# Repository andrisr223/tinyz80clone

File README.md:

# tinyz80clone

A Z80 board based on [tiny z80](https://github.com/skiselev/tiny_z80) and [
2063-Z80](https://github.com/Z80-Retro/2063-Z80).
For glue logic SLG46826V is used (a single cpld with more legs/gates would be more appropriate).

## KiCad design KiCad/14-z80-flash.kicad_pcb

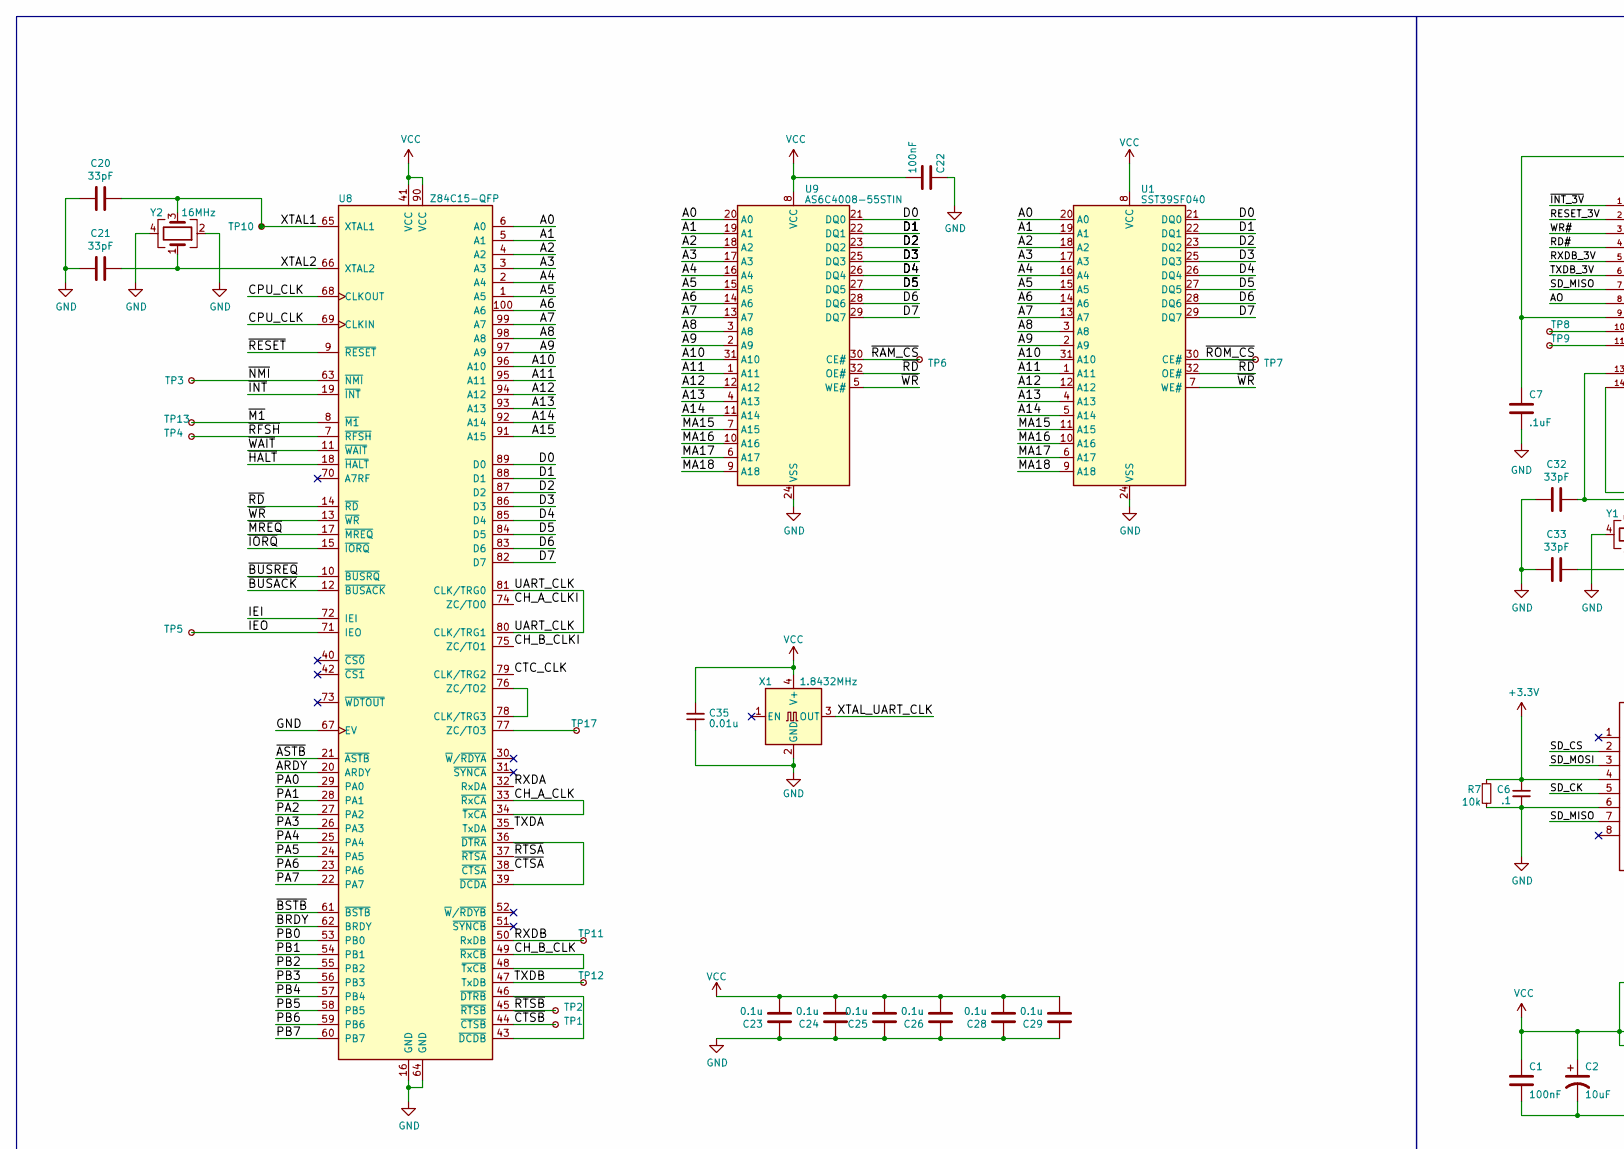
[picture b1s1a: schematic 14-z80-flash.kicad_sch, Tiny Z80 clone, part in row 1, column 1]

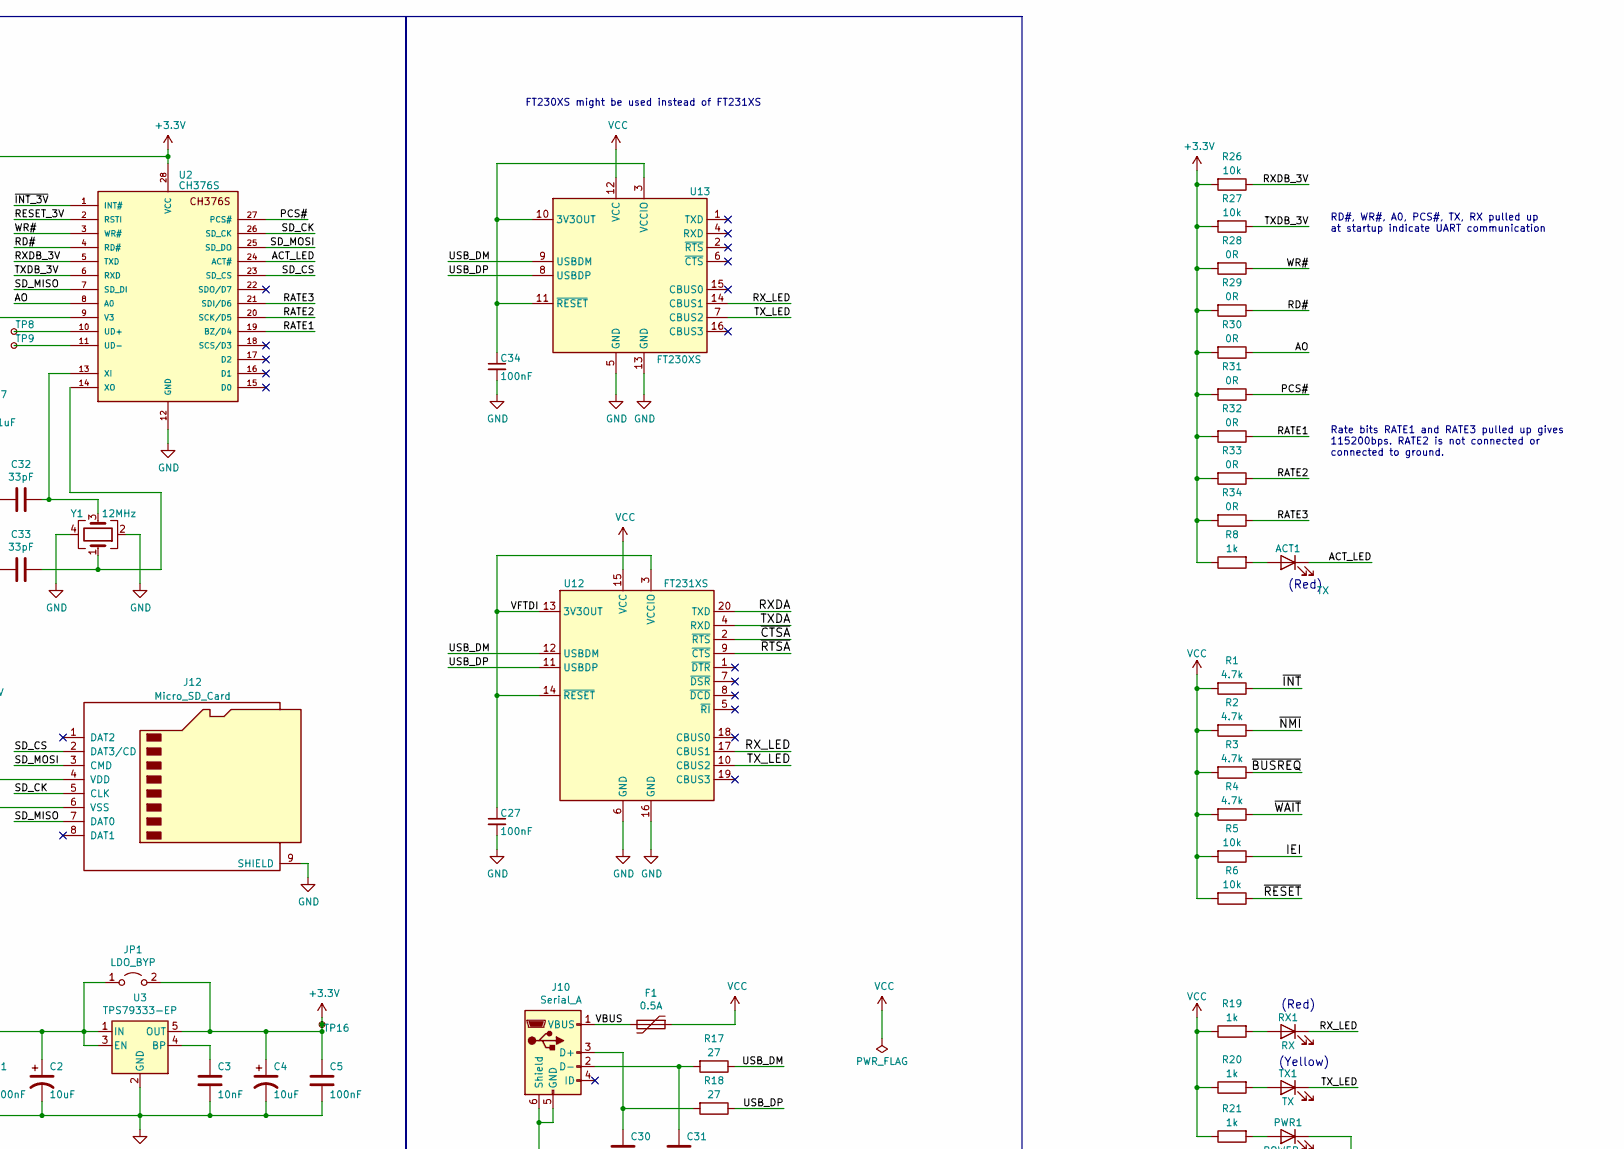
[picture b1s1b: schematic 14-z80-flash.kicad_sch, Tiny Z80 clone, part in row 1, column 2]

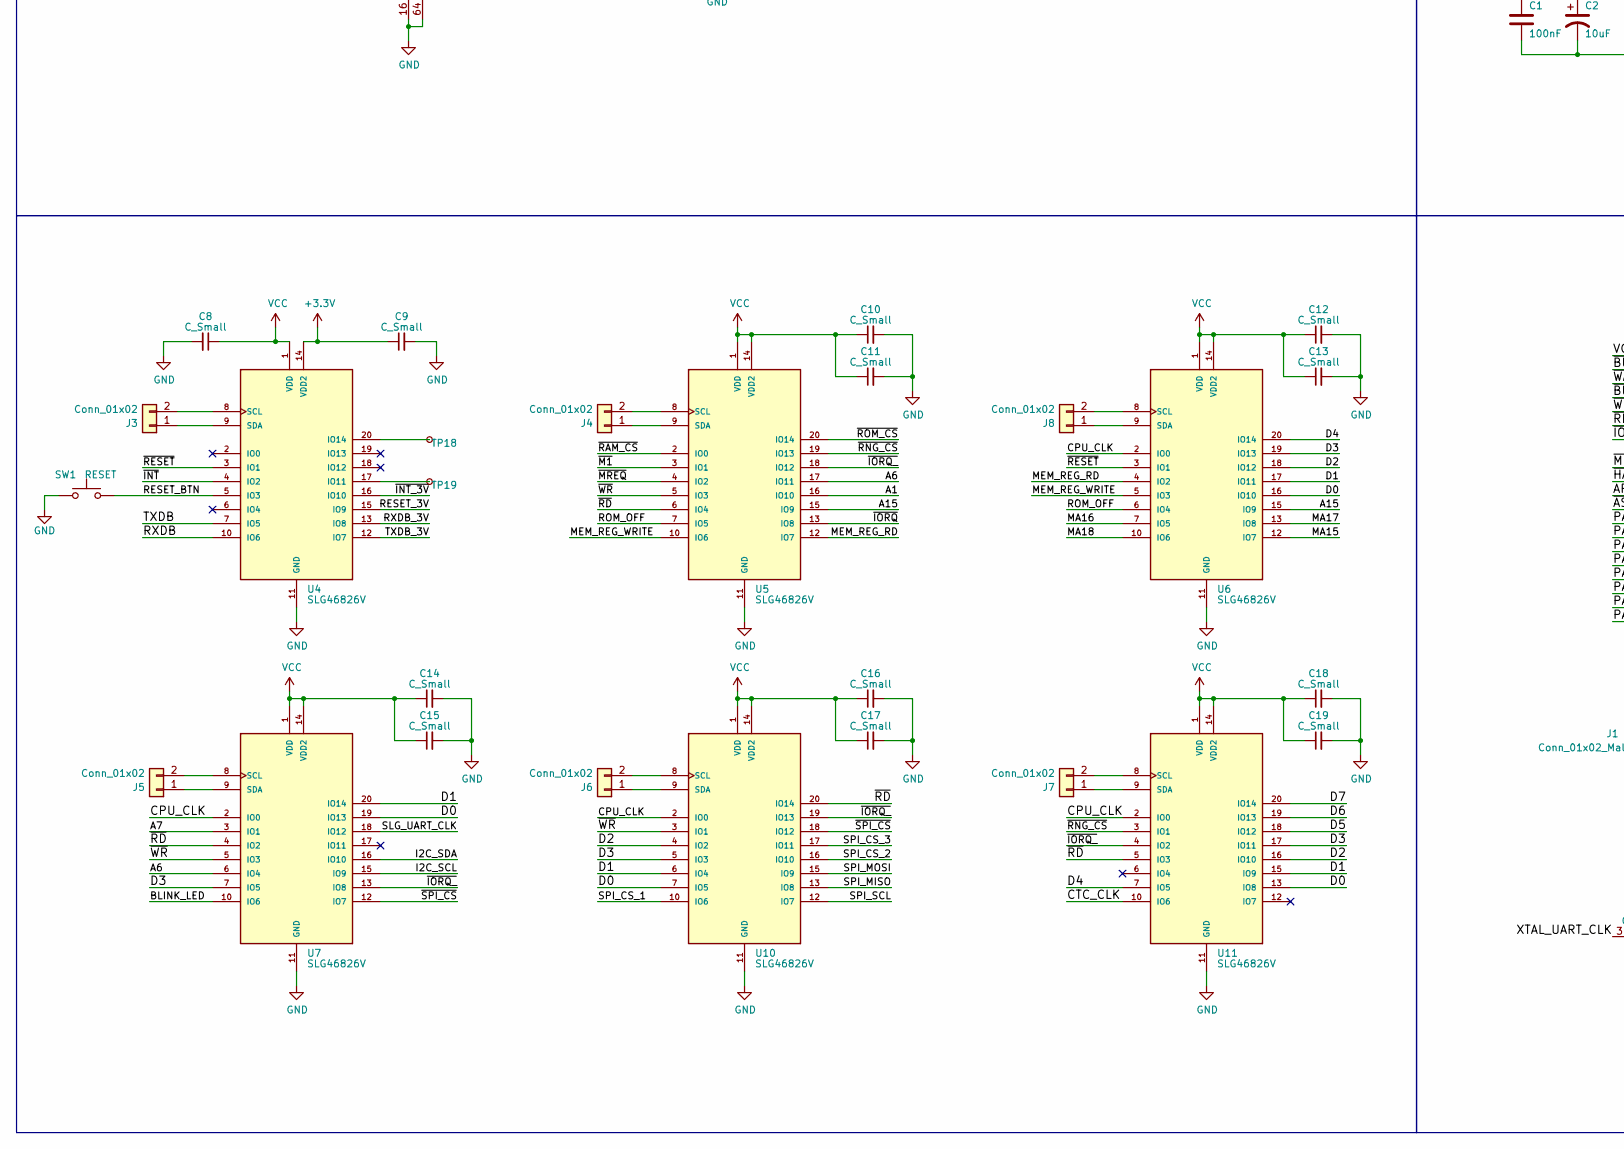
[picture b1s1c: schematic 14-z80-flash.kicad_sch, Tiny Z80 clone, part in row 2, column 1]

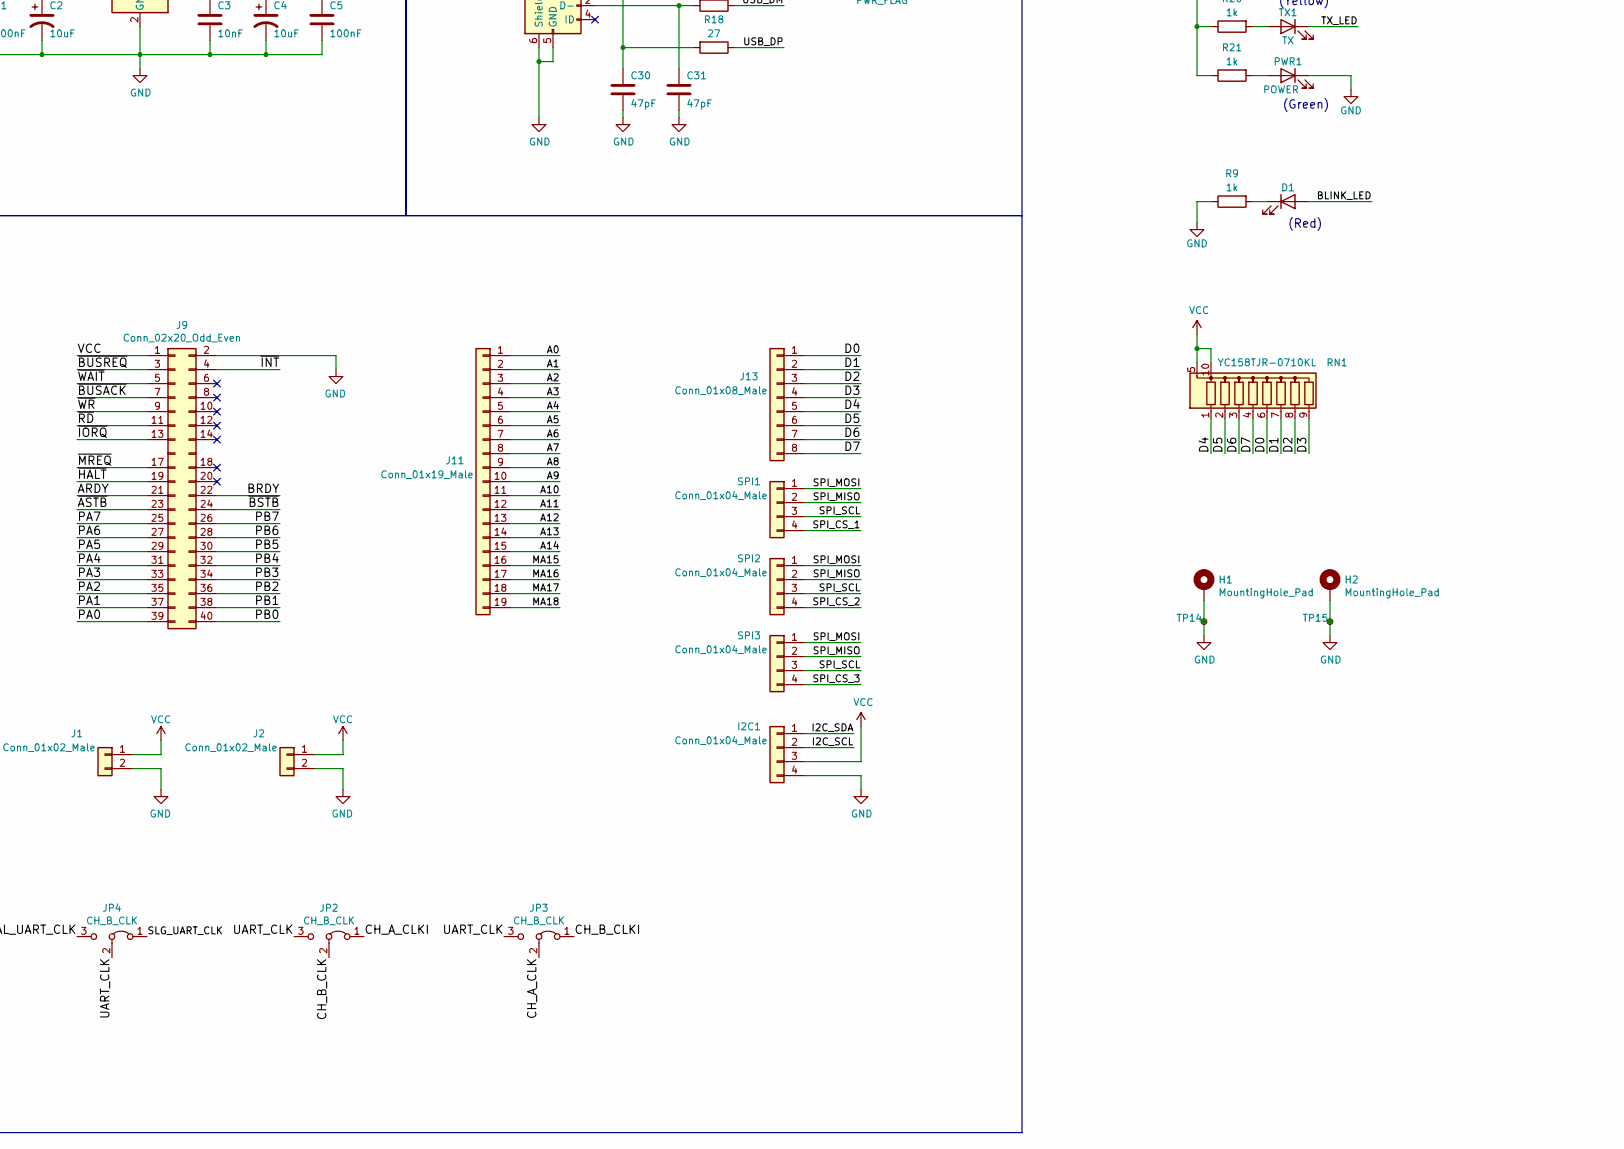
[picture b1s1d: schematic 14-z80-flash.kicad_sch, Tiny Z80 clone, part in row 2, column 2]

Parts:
ACT1: TX; LED_0805_2012Metric_Pad1.15x1.40mm_HandSolder
C1, C5, C22: 100nF; C_0603_1608Metric_Pad1.08x0.95mm_HandSolder
C2, C4: 10uF; CP_EIA-6032-28_Kemet-C_Pad2.25x2.35mm_HandSolder
C3: 10nF; C_0603_1608Metric_Pad1.08x0.95mm_HandSolder
C6: .1; C_0805_2012Metric_Pad1.18x1.45mm_HandSolder
C7: .1uF; C_0805_2012Metric_Pad1.18x1.45mm_HandSolder
C8, C9, C10, C11, C12, C13, C14, C15, C16, C17, C18, C19: C_Small; C_0402_1005Metric_Pad0.74x0.62mm_HandSolder
C20, C21: 33pF; C_0603_1608Metric_Pad1.08x0.95mm_HandSolder
C23, C24, C25, C26, C28, C29: 0.1u; C_0603_1608Metric_Pad1.08x0.95mm_HandSolder
C27, C34: 100nF; C_0805_2012Metric_Pad1.18x1.45mm_HandSolder
C30, C31: 47pF; C_0805_2012Metric_Pad1.18x1.45mm_HandSolder
C32, C33: 33pF; C_0805_2012Metric_Pad1.18x1.45mm_HandSolder
C35: 0.01u; C_0805_2012Metric_Pad1.18x1.45mm_HandSolder
D1: TX; LED_0805_2012Metric_Pad1.15x1.40mm_HandSolder
F1: 0.5A; Fuse_1812_4532Metric_Pad1.30x3.40mm_HandSolder
H1, H2: MountingHole_Pad; MountingHole_2.7mm_M2.5_Pad_Via
I2C1: Conn_01x04_Male; Molex_PicoBlade_53048-0410_1x04_P1.25mm_Horizontal
J1: Conn_01x02_Male; Molex_PicoBlade_53048-0210_1x02_P1.25mm_Horizontal
J2: Conn_01x02_Male; PinHeader_1x02_P2.54mm_Vertical
J3, J4, J5, J6, J7, J8: Conn_01x02; SlgI2C-Pad0.5x1.5mm
J9: Conn_02x20_Odd_Even; Samtec_MECF-20-0_-L-DV_2x20_P1.27mm_Polarized_Edge
J10: Serial_A; USB_Micro-B_WuerthMod_629105150521_CircularHoles
J11: Conn_01x19_Male; PinHeader_1x19_P2.54mm_Vertical
J12: Micro_SD_Card; microSD_HC_Wuerth_693072010801
J13: Conn_01x08_Male; PinHeader_1x08_P2.54mm_Vertical
JP1: LDO_BYP; SolderJumper-2_P1.3mm_Open_RoundedPad1.0x1.5mm
JP2, JP3, JP4: CH_B_CLK; SolderJumper-3_P1.3mm_Open_RoundedPad1.0x1.5mm_NumberLabels
PWR1: POWER; LED_0805_2012Metric_Pad1.15x1.40mm_HandSolder
R1, R2, R3, R4: 4.7k; R_0603_1608Metric_Pad0.98x0.95mm_HandSolder
R5, R6: 10k; R_0603_1608Metric_Pad0.98x0.95mm_HandSolder
R7: 10k; R_0805_2012Metric_Pad1.20x1.40mm_HandSolder
R8, R9, R19, R20, R21: 1k; R_0805_2012Metric_Pad1.20x1.40mm_HandSolder
R17, R18: 27; R_0805_2012Metric_Pad1.20x1.40mm_HandSolder
R26, R27: 10k; R_0402_1005Metric_Pad0.72x0.64mm_HandSolder
R28, R29, R30, R31, R32, R33, R34: 0R; R_0402_1005Metric_Pad0.72x0.64mm_HandSolder
RN1: YC158TJR-0710KL; RESCAXE64P320X160X70-10N
RX1: RX; LED_0805_2012Metric_Pad1.15x1.40mm_HandSolder
SPI1, SPI2, SPI3: Conn_01x04_Male; Molex_PicoBlade_53048-0410_1x04_P1.25mm_Horizontal
SW1: RESET; SW_SPST_B3U-1000P-B
TP1, TP2, TP3, TP4, TP5, TP6, TP7, TP8, TP9, TP10, TP11, TP12, TP13, TP16, TP17, TP18, TP19: U2_10; TestPoint_Pad_0.8x0.8mm
TP14, TP15: U2_10; TestPoint_THTPad_1.5x1.5mm_Drill0.7mm
TX1: TX; LED_0805_2012Metric_Pad1.15x1.40mm_HandSolder
U1: SST39SF040; TSOP-I-32_14.4x8mm_P0.5mm
U2: CH376S; CH376S-SOP28-P1.29mm
U3: TPS79333-EP; SOT-23-5
U4, U5, U6, U7, U10, U11: SLG46826V; IC_SLG46826V; PARTREV 3.10
U8: Z84C15-QFP; PQFP-100_14x20mm_P0.65mm
U9: AS6C4008-55STIN; TSOP-I-32_12.4x8mm_P0.5mm
U12: FT231XS; SSOP-20_3.9x8.7mm_P0.635mm
U13: FT230XS; SSOP-16_3.9x4.9mm_P0.635mm
X1: 1.8432MHz; Oscillator_SMD_EuroQuartz_XO91-4Pin_7.0x5.0mm
Y1: 12MHz; Crystal_SMD_3225-4Pin_3.2x2.5mm_HandSoldering
Y2: 16MHz; Crystal_SMD_3225-4Pin_3.2x2.5mm_HandSoldering

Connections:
+3V3: C4.1, C5.1, C6.1, C7.1, C9.1, J12.4 (VDD), JP1.2 (B), R7.1, R8.1, R26.2, R27.2, R28.2, R29.2, R30.2, R31.2, R32.2, R33.2, R34.2, TP16.1, U2.9 (V3), U2.28 (VCC), U3.5 (OUT), U4.14 (VDD2)
/A0: J11.1, U1.20 (A0), U8.6 (A0), U9.20 (A0)
/A1: J11.2, U1.19 (A1), U5.16 (IO10), U8.5 (A1), U9.19 (A1)
/A2: J11.3, U1.18 (A2), U8.4 (A2), U9.18 (A2)
/A3: J11.4, U1.17 (A3), U8.3 (A3), U9.17 (A3)
/A4: J11.5, U1.16 (A4), U8.2 (A4), U9.16 (A4)
/A5: J11.6, U1.15 (A5), U8.1 (A5), U9.15 (A5)
/A6: J11.7, U1.14 (A6), U5.17 (IO11), U7.6 (IO4), U8.100 (A6), U9.14 (A6)
/A7: J11.8, U1.13 (A7), U7.3 (IO1), U8.99 (A7), U9.13 (A7)
/A8: J11.9, U1.3 (A8), U8.98 (A8), U9.3 (A8)
/A9: J11.10, U1.2 (A9), U8.97 (A9), U9.2 (A9)
/A10: J11.11, U1.31 (A10), U8.96 (A10), U9.31 (A10)
/A11: J11.12, U1.1 (A11), U8.95 (A11), U9.1 (A11)
/A12: J11.13, U1.12 (A12), U8.94 (A12), U9.12 (A12)
/A13: J11.14, U1.4 (A13), U8.93 (A13), U9.4 (A13)
/A14: J11.15, U1.5 (A14), U8.92 (A14), U9.11 (A14)
/A15: U5.15 (IO9), U6.15 (IO9), U8.91 (A15)
/ACT_LED: ACT1.1 (K), U2.24 (ACT#)
/AO: R30.1, U2.8 (A0)
/ARDY: J9.21, U8.20 (ARDY)
/BLINK_LED: D1.2 (A), U7.10 (IO6)
/BRDY: J9.22, U8.62 (BRDY)
/CH_A_CLK: JP3.2 (C), U8.33 (~RxCA), U8.34 (~TxCA)
/CH_A_CLKI: JP2.1 (A), U8.74 (ZC/TO0)
/CH_B_CLK: JP2.2 (C), U8.48 (~TxCB), U8.49 (~RxCB)
/CH_B_CLKI: JP3.1 (A), U8.75 (ZC/TO1)
/CPU_CLK: U6.2 (IO0), U7.2 (IO0), U8.68 (CLKOUT), U8.69 (CLKIN), U10.2 (IO0), U11.2 (IO0)
/CTC_CLK: U8.79 (CLK/TRG2), U11.10 (IO6)
/D0: J13.1, RN1.6 (R5), U1.21 (DQ0), U6.16 (IO10), U7.19 (IO13), U8.89 (D0), U9.21 (DQ0), U10.7 (IO5), U11.13 (IO8)
/D1: J13.2, RN1.7 (R6), U1.22 (DQ1), U6.17 (IO11), U7.20 (IO14), U8.88 (D1), U9.22 (DQ1), U10.6 (IO4), U11.15 (IO9)
/D2: J13.3, RN1.8 (R7), U1.23 (DQ2), U6.18 (IO12), U8.87 (D2), U9.23 (DQ2), U10.4 (IO2), U11.16 (IO10)
/D3: J13.4, RN1.9 (R8), U1.25 (DQ3), U6.19 (IO13), U7.7 (IO5), U8.86 (D3), U9.25 (DQ3), U10.5 (IO3), U11.17 (IO11)
/D4: J13.5, RN1.1 (R1), U1.26 (DQ4), U6.20 (IO14), U8.85 (D4), U9.26 (DQ4), U11.7 (IO5)
/D5: J13.6, RN1.2 (R2), U1.27 (DQ5), U8.84 (D5), U9.27 (DQ5), U11.18 (IO12)
/D6: J13.7, RN1.3 (R3), U1.28 (DQ6), U8.83 (D6), U9.28 (DQ6), U11.19 (IO13)
/D7: J13.8, RN1.4 (R4), U1.29 (DQ7), U8.82 (D7), U9.29 (DQ7), U11.20 (IO14)
/I2C_SCL: I2C1.2, U7.15 (IO9)
/I2C_SDA: I2C1.1, U7.16 (IO10)
/IEI: R5.1, U8.72 (IEI)
/IEO: TP5.1, U8.71 (IEO)
/MA15: J11.16, U1.11 (A15), U6.12 (IO7), U9.7 (A15)
/MA16: J11.17, U1.10 (A16), U6.7 (IO5), U9.10 (A16)
/MA17: J11.18, U1.6 (A17), U6.13 (IO8), U9.6 (A17)
/MA18: J11.19, U1.9 (A18), U6.10 (IO6), U9.9 (A18)
/MEM_REG_RD: U5.12 (IO7), U6.4 (IO2)
/MEM_REG_WRITE: U5.10 (IO6), U6.5 (IO3)
/PA0: J9.39, U8.29 (PA0)
/PA1: J9.37, U8.28 (PA1)
/PA2: J9.35, U8.27 (PA2)
/PA3: J9.33, U8.26 (PA3)
/PA4: J9.31, U8.25 (PA4)
/PA5: J9.29, U8.24 (PA5)
/PA6: J9.27, U8.23 (PA6)
/PA7: J9.25, U8.22 (PA7)
/PB0: J9.40, U8.53 (PB0)
/PB1: J9.38, U8.54 (PB1)
/PB2: J9.36, U8.55 (PB2)
/PB3: J9.34, U8.56 (PB3)
/PB4: J9.32, U8.57 (PB4)
/PB5: J9.30, U8.58 (PB5)
/PB6: J9.28, U8.59 (PB6)
/PB7: J9.26, U8.60 (PB7)
/PCS#: R31.1, U2.27 (PCS#)
/RATE1: R32.1, U2.19 (BZ/D4)
/RATE2: R33.1, U2.20 (SCK/D5)
/RATE3: R34.1, U2.21 (SDI/D6)
/RD#: R29.1, U2.4 (RD#)
/RESET_3V: U2.2 (RSTI), U4.15 (IO9)
/RESET_BTN: SW1.1, U4.5 (IO3)
/ROM_OFF: U5.7 (IO5), U6.6 (IO4)
/RXDA: U8.32 (RxDA), U12.20 (TXD)
/RXDB: TP11.1, U4.10 (IO6), U8.50 (RxDB)
/RXDB_3V: R26.1, U2.5 (TXD), U4.13 (IO8)
/RX_LED: RX1.1 (K), U12.17 (CBUS1), U13.14 (CBUS1)
/SD_CK: J12.5 (CLK), U2.26 (SD_CK)
/SD_CS: J12.2 (DAT3/CD), U2.23 (SD_CS)
/SD_MISO: J12.7 (DAT0), U2.7 (SD_DI)
/SD_MOSI: J12.3 (CMD), U2.25 (SD_DO)
/SLG_UART_CLK: JP4.1 (A), U7.18 (IO12)
/SPI_CS_1: SPI1.4, U10.10 (IO6)
/SPI_CS_2: SPI2.4, U10.16 (IO10)
/SPI_CS_3: SPI3.4, U10.17 (IO11)
/SPI_MISO: SPI1.2, SPI2.2, SPI3.2, U10.13 (IO8)
/SPI_MOSI: SPI1.1, SPI2.1, SPI3.1, U10.15 (IO9)
/SPI_SCL: SPI1.3, SPI2.3, SPI3.3, U10.12 (IO7)
/TXDA: U8.35 (TxDA), U12.4 (RXD)
/TXDB: TP12.1, U4.7 (IO5), U8.47 (TxDB)
/TXDB_3V: R27.1, U2.6 (RXD), U4.12 (IO7)
/TX_LED: TX1.1 (K), U12.10 (CBUS2), U13.7 (CBUS2)
/UART_CLK: JP2.3 (B), JP3.3 (B), JP4.2 (C), U8.80 (CLK/TRG1), U8.81 (CLK/TRG0)
/USB_DM: R17.1, U12.12 (USBDM), U13.9 (USBDM)
/USB_DP: R18.1, U12.11 (USBDP), U13.8 (USBDP)
/VBUS: F1.2, J10.1 (VBUS)
/VFTDI: C27.1, U12.3 (VCCIO), U12.13 (3V3OUT), U12.14 (~RESET)
/WR#: R28.1, U2.3 (WR#)
/XTAL1: C20.1, TP10.1, U8.65 (XTAL1), Y2.3
/XTAL2: C21.1, U8.66 (XTAL2), Y2.1
/XTAL_UART_CLK: JP4.3 (B), X1.3 (OUT)
/~ASTB: J9.23, U8.21 (~ASTB)
/~BSTB: J9.24, U8.61 (~BSTB)
/~BUSACK: J9.7, U8.12 (~BUSACK)
/~BUSREQ: J9.3, R3.1, U8.10 (~BUSRQ)
/~CTSA: U8.38 (~CTSA), U12.2 (~RTS)
/~CTSB: TP1.1, U8.44 (~CTSB)
/~HALT: J9.19, U8.18 (~HALT)
/~INT_3V: U2.1 (INT#), U4.16 (IO10)
/~INT: J9.4, R1.1, U4.4 (IO2), U8.19 (~INT)
/~IORQ_: U5.18 (IO12), U7.13 (IO8), U10.19 (IO13), U11.4 (IO2)
/~IORQ: J9.13, U5.13 (IO8), U8.15 (~IORQ)
/~M1: TP13.1, U5.3 (IO1), U8.8 (~M1)
/~MREQ: J9.17, U5.4 (IO2), U8.17 (~MREQ)
/~NMI: R2.1, TP3.1, U8.63 (~NMI)
/~RAM_CS: TP6.1, U5.2 (IO0), U9.30 (CE#)
/~RD: J9.11, U1.32 (OE#), U5.6 (IO4), U7.4 (IO2), U8.14 (~RD), U9.32 (OE#), U10.20 (IO14), U11.5 (IO3)
/~RESET: R6.1, U4.3 (IO1), U6.3 (IO1), U8.9 (~RESET)
/~RFSH: TP4.1, U8.7 (~RFSH)
/~RNG_CS: U5.19 (IO13), U11.3 (IO1)
/~ROM_CS: TP7.1, U1.30 (CE#), U5.20 (IO14); also elsewhere on the board
/~RTSA: U8.37 (~RTSA), U12.9 (~CTS)
/~RTSB: TP2.1, U8.45 (~RTSB)
/~SPI_CS: U7.12 (IO7), U10.18 (IO12)
/~WAIT: J9.5, R4.1, U8.11 (~WAIT)
/~WR: J9.9, U1.7 (WE#), U5.5 (IO3), U7.5 (IO3), U8.13 (~WR), U9.5 (WE#), U10.3 (IO1)
GND: C1.2, C2.2, C3.2, C4.2, C5.2, C6.2, C7.2, C8.2, C9.2, C10.2, C11.2, C12.2, C13.2, C14.2, C15.2, C16.2, C17.2, C18.2, C19.2, C20.2, C21.2, C22.1, C23.1, C24.1, C25.1, C26.1, C27.2, C28.1, C29.1, C30.2, C31.2, C32.2, C33.2, C34.2, C35.1, H1.1, H2.1, I2C1.4, J1.2, J2.2, J9.2, J10.5 (GND), J10.6 (Shield), J12.6 (VSS), J12.9 (SHIELD), PWR1.1 (K), R7.2, R9.1, SW1.2, TP14.1, TP15.1, U1.24 (VSS), U2.12 (GND), U3.2 (GND), U4.11 (GND), U5.11 (GND), U6.11 (GND), U7.11 (GND), U8.16 (GND), U8.64 (GND), U8.67 (EV), U9.24 (VSS), U10.11 (GND), U11.11 (GND), U12.6 (GND), U12.16 (GND), U13.5 (GND), U13.13 (GND), X1.2 (GND), Y1.2, Y1.4, Y2.2, Y2.4
unnamed: ACT1.2 (A), R8.2
unnamed: C34.1, U13.3 (VCCIO), U13.10 (3V3OUT), U13.11 (~RESET)
unnamed: D1.1 (K), R9.2
unnamed: J3.1, U4.9 (SDA)
unnamed: J3.2, U4.8 (SCL)
unnamed: J4.1, U5.9 (SDA)
unnamed: J4.2, U5.8 (SCL)
unnamed: J5.1, U7.9 (SDA)
unnamed: J5.2, U7.8 (SCL)
unnamed: J6.1, U10.9 (SDA)
unnamed: J6.2, U10.8 (SCL)
unnamed: J7.1, U11.9 (SDA)
unnamed: J7.2, U11.8 (SCL)
unnamed: J8.1, U6.9 (SDA)
unnamed: J8.2, U6.8 (SCL)
unnamed: C30.1, J10.3 (D+), R18.2
unnamed: C31.1, J10.2 (D-), R17.2
unnamed: PWR1.2 (A), R21.2
unnamed: R19.2, RX1.2 (A)
unnamed: R20.2, TX1.2 (A)
unnamed: TP8.1, U2.10 (UD+)
unnamed: TP9.1, U2.11 (UD-)
unnamed: C32.1, U2.13 (XI), Y1.3
unnamed: C33.1, U2.14 (XO), Y1.1
unnamed: C3.1, U3.4 (BP)
unnamed: TP19.1, U4.17 (IO11)
unnamed: TP18.1, U4.20 (IO14)
unnamed: U8.76 (ZC/TO2), U8.78 (CLK/TRG3)
unnamed: TP17.1, U8.77 (ZC/TO3)
unnamed: U8.36 (~DTRA), U8.39 (~DCDA)
unnamed: U8.43 (~DCDB), U8.46 (~DTRB)
VCC: C1.1, C2.1, C8.1, C10.1, C11.1, C12.1, C13.1, C14.1, C15.1, C16.1, C17.1, C18.1, C19.1, C22.2, C23.2, C24.2, C25.2, C26.2, C28.2, C29.2, C35.2, F1.1, I2C1.3, J1.1, J2.1, J9.1, JP1.1 (A), R1.2, R2.2, R3.2, R4.2, R5.2, R6.2, R19.1, R20.1, R21.1, RN1.5 (R4), RN1.10 (common), U1.8 (VCC), U3.1 (IN), U3.3 (EN), U4.1 (VDD), U5.1 (VDD), U5.14 (VDD2), U6.1 (VDD), U6.14 (VDD2), U7.1 (VDD), U7.14 (VDD2), U8.41 (VCC), U8.90 (VCC), U9.8 (VCC), U10.1 (VDD), U10.14 (VDD2), U11.1 (VDD), U11.14 (VDD2), U12.15 (VCC), U13.12 (VCC), X1.4 (V+)

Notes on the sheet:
(Yellow)
(Red)
Rate bits RATE1 and RATE3 pulled up gives 115200bps. RATE2 is not connected or connected to ground.
(Green)
FT230XS might be used instead of FT231XS
RD#, WR#, A0, PCS#, TX, RX pulled up at startup indicate UART communication

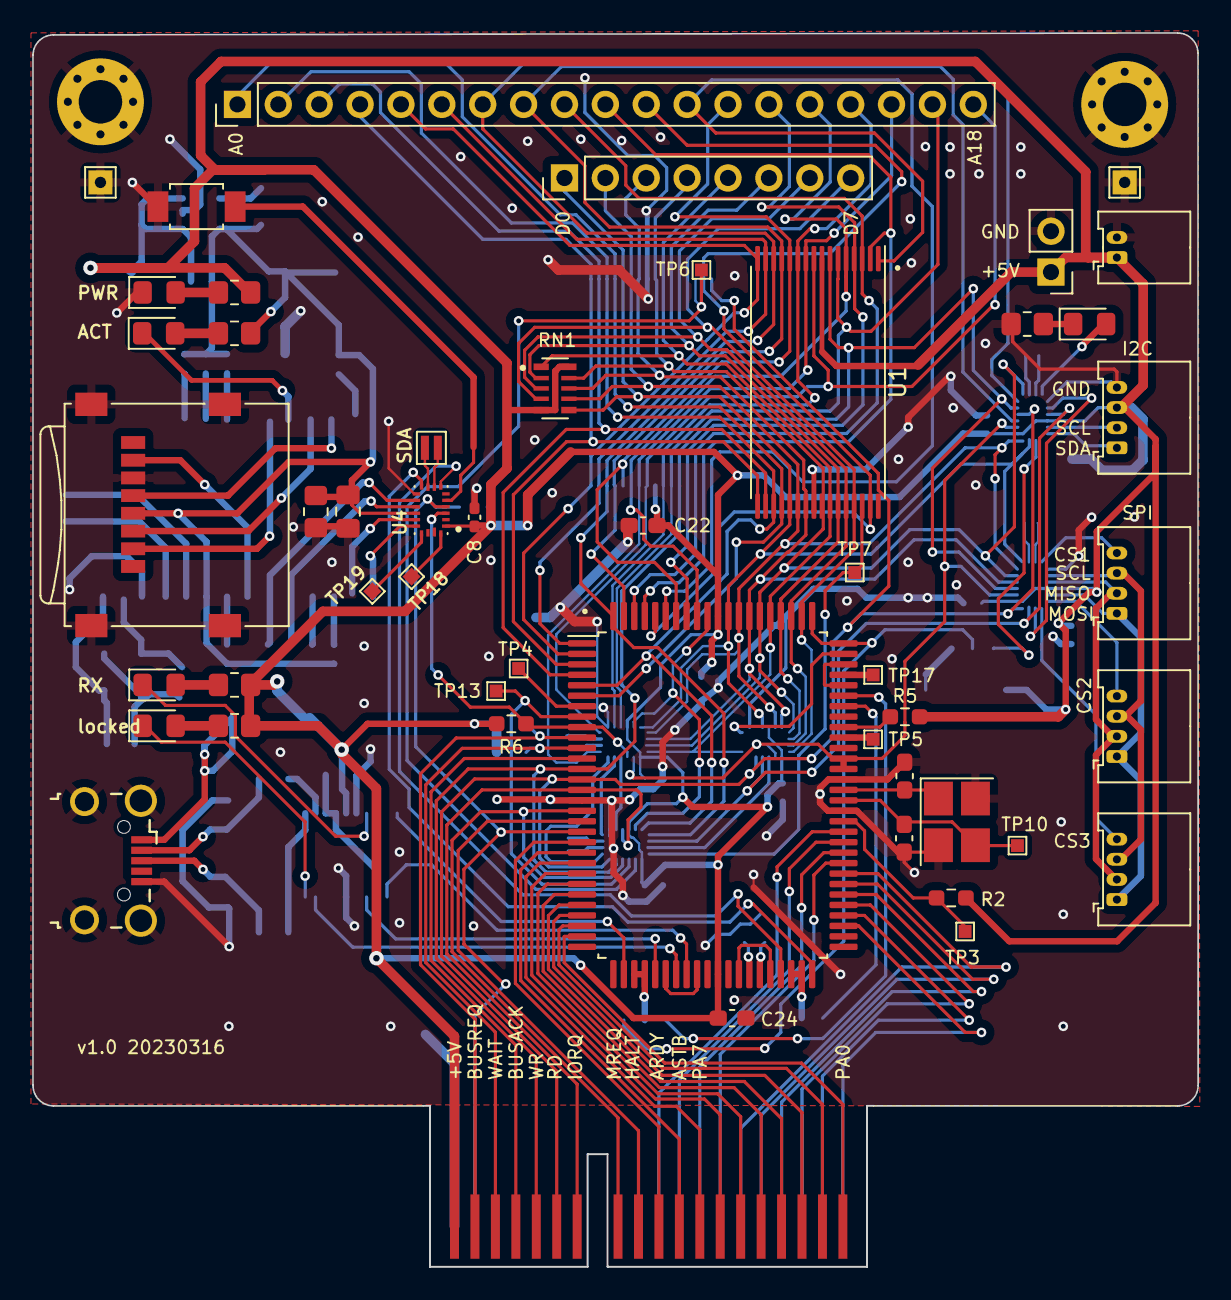
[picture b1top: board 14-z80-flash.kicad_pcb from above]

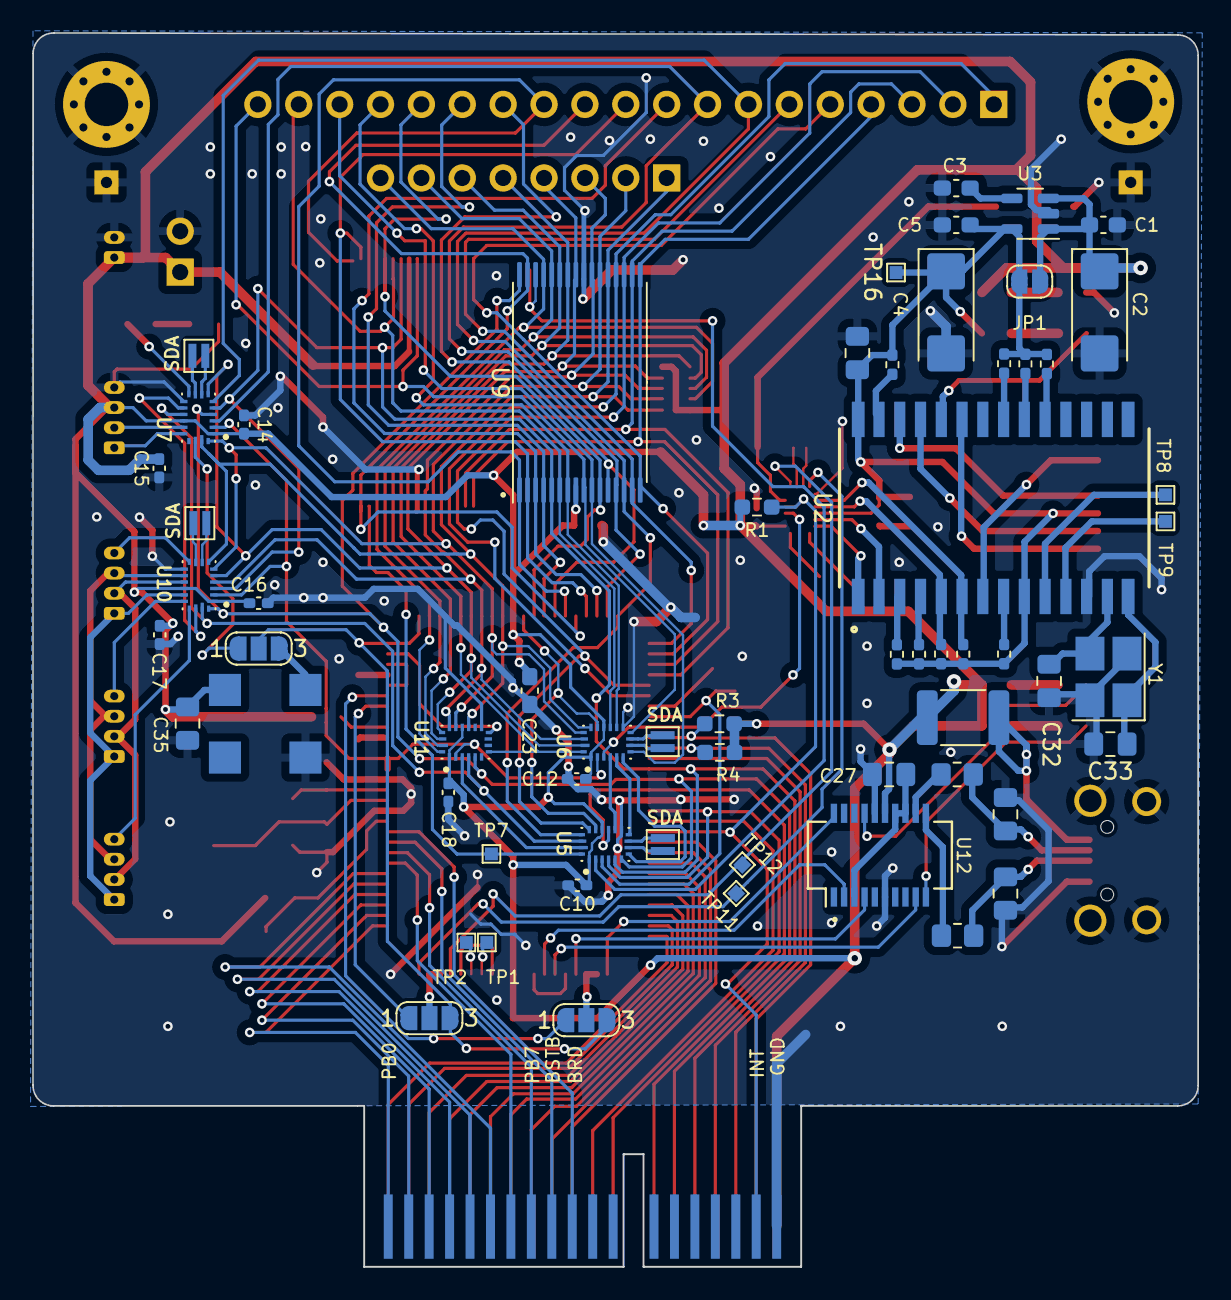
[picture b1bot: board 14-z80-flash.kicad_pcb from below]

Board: 2 copper layers, 72.4 x 76.7 mm, 114 parts (62 on the bottom side), 153 nets.

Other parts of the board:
TP7#2: U2_10; TestPoint_Pad_0.8x0.8mm

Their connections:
/~ROM_CS: TP7#2.1; also elsewhere on the board

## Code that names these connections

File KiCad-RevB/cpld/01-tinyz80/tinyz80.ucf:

# clock signals
NET "CPU_CLK" LOC = "P15" ;
NET "CPU_CLK" BUFG = CLK ;

NET "UART_CLK" LOC = "P34" ;

NET "CPU_CLK_3V_B" LOC = "P16" ;
NET "CPU_CLK_3V_B" BUFG = CLK ;

NET "CPU_CLK_3V" LOC = "P51" ;

# chip selects
NET "RNG_CSn" LOC = "P19" ;
NET "RAM_CSn" LOC = "P20" ;
NET "ROM_CSn" LOC = "P22" ;
NET "I2C_CSn" LOC = "P35" ;
NET "SPI_CSn" LOC = "P36" ;

# LED_OUT
# test pin, EX0 on debug connector
NET "LED_OUT" LOC = "P40" ;
# EX1 on debug connector
NET "LED_OUT" LOC = "P42" ;

# TN-
NET "MODE" LOC = "P46" ;
NET "CSR_CSn" LOC = "P47" ;
NET "CSN_CSn" LOC = "P48" ;
NET "GROM_CLK" LOC = "P52" ;
# SID
# SID chip has 32 registers but only 2 (4) pins are available
# It will be necessary to write to aregister in two steps:
# * select a register
# * write a value to the selected register
NET "CSS_CSn" LOC = "P50" ;

# Z80 signals
NET "WR" LOC = "P58" ;
NET "RD" LOC = "P57" ;

NET "M1" LOC = "P60" ;
NET "MREQ" LOC = "P44" ;
NET "IORQ" LOC = "P43" ;
# TODO necessary?
# NET "INT3V3" LOC = "P49" ;

NET "RSTn" LOC = "P59" ;
# NET "RESET_3V" LOC = "P56" ;

# -- https://www.edaboard.com/threads/how-to-write-the-ucf-file-in-xilinx-for-array-variables.316709/
NET D<0> LOC = "P8" ;
NET D<1> LOC = "P9" ;
NET D<2> LOC = "P10" ;
NET D<3> LOC = "P11" ;
NET D<4> LOC = "P12" ;
NET D<5> LOC = "P13" ;
NET D<6> LOC = "P18" ;
NET D<7> LOC = "P17" ;

NET "A<0>" LOC = "P62" ;
NET "A<1>" LOC = "P61" ;
NET "A<2>" LOC = "P63" ;
NET "A<3>" LOC = "P64" ;
NET "A<4>" LOC = "P1" ;
NET "A<5>" LOC = "P2" ;
NET "A<6>" LOC = "P4" ;
NET "A<7>" LOC = "P5" ;

NET "A_HI<14>" LOC = "P6" ;
NET "A_HI<15>" LOC = "P7" ;

NET "MA<14>" LOC = "P23" ;
NET "MA<15>" LOC = "P24" ;
NET "MA<16>" LOC = "P25" ;
NET "MA<17>" LOC = "P27" ;
NET "MA<18>" LOC = "P31" ;


# SD card
NET "SD_DETECT" LOC = "P32" ;

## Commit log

2023-04-01 KiCad files
2023-04-14 Fixes for glue logic
    * Fixed reset button issue, consider it active low and add a pullup
    resistor to the pin.
    * Use open drain for the reset pin as per Z84 datasheet (push pull might
    damage the chip?)
    * Fixed chip select in i2c interface chip, use active low for chip select.
2023-04-14 Added blink example
2023-05-07 Disconnect Ch376 interrupt
    Do not connect Ch376 interrupt line to the CPU INT pin; use Ch376
    GET_STATUS command to read the interrupt status in UART mode.
    If necessary, a separate register would be better to read this
    interrupt.
    Keep the three oscillators always running in the RNG register chip. If
    they are turned on only when a value is requested, the results are not
2023-05-14 Added shell example
2023-06-11 RW support
2023-10-15 Added revision B KiCad files
